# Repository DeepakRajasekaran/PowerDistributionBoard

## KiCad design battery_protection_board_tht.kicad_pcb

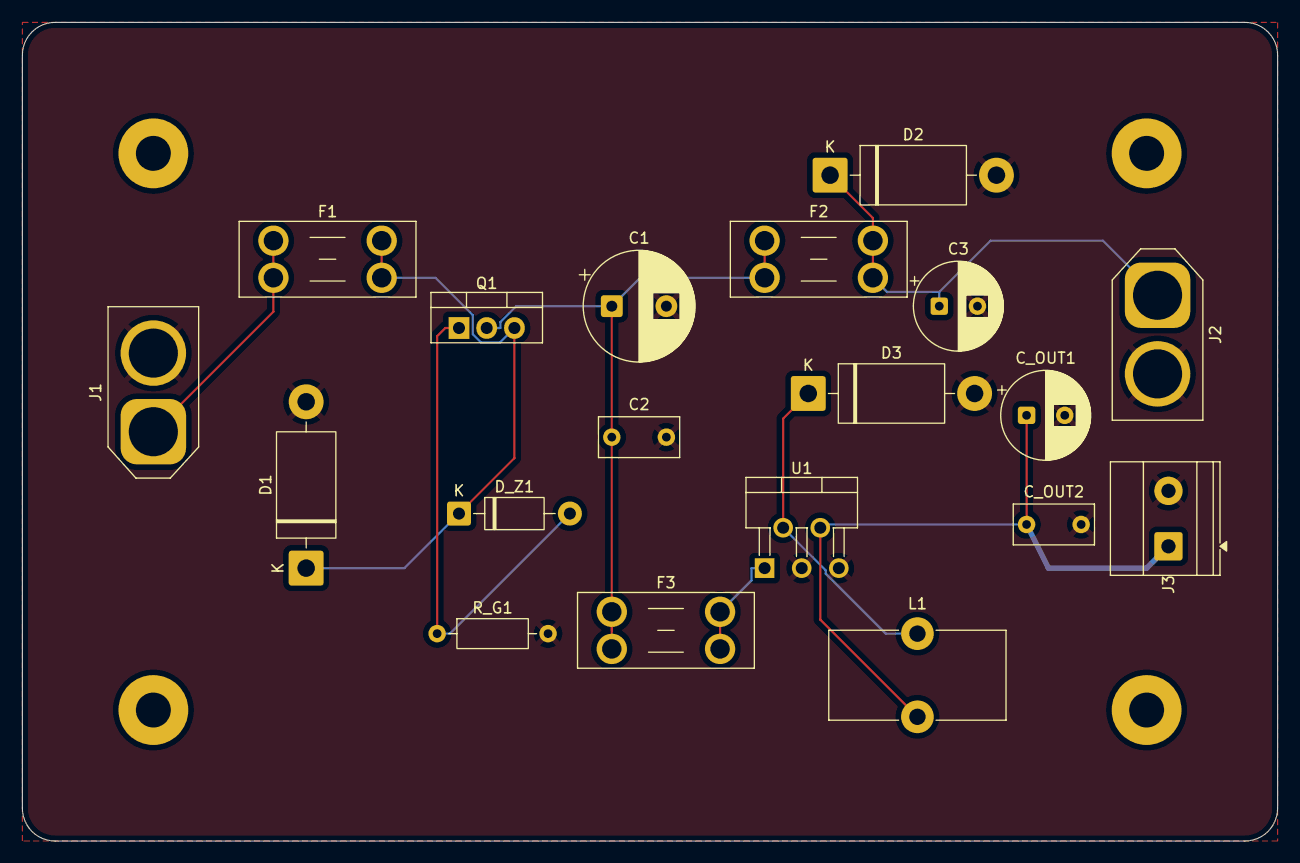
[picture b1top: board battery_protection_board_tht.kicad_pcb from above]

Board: 2 copper layers, 115.0 x 75.0 mm, 23 parts (0 on the bottom side), 9 nets.

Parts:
C1: 470uF 35V; CP_Radial_D10.0mm_P5.00mm
C2: 100nF 50V; C_Rect_L7.2mm_W3.5mm_P5.00mm_FKS2_FKP2_MKS2_MKP2
C3: 100uF 35V; CP_Radial_D8.0mm_P3.50mm
C_OUT1: 470uF 16V; CP_Radial_D8.0mm_P3.50mm
C_OUT2: 100nF 50V; C_Rect_L7.2mm_W3.5mm_P5.00mm_FKS2_FKP2_MKS2_MKP2
D1: 1.5KE18CA; D_DO-201AD_P15.24mm_Horizontal
D2: 1.5KE18A; D_DO-201AD_P15.24mm_Horizontal
D3: 1N5822; D_DO-201AD_P15.24mm_Horizontal
D_Z1: 1N4742A_12V; D_DO-41_SOD81_P10.16mm_Horizontal
F1: 15A Blade; Fuseholder_Blade_Mini_Keystone_3568
F2: 10A Blade; Fuseholder_Blade_Mini_Keystone_3568
F3: 3A Blade; Fuseholder_Blade_Mini_Keystone_3568
J1: XT60-M_BATT_IN; AMASS_XT60-M_1x02_P7.20mm_Vertical
J2: XT60-F_OUT2_10A; AMASS_XT60-F_1x02_P7.20mm_Vertical
J3: 5V_3A_TERM; TerminalBlock_Phoenix_MKDS-1,5-2-5.08_1x02_P5.08mm_Horizont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
L1: 33uH 5A; L_Toroid_Vertical_L16.0mm_W8.0mm_P7.62mm
MH1, MH2, MH3, MH4: MountingHole_3.2mm; MountingHole_3.2mm_M3_Pad
Q1: IRF4905; TO-220-3_Vertical
R_G1: 100k; R_Axial_DIN0207_L6.3mm_D2.5mm_P10.16mm_Horizontal
U1: LM2596T-5.0; TO-220-5_P3.4x3.7mm_StaggerOdd_Lead3.8mm_Vertical

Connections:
+5V: C_OUT1.1, C_OUT2.1, J3.1, L1.2, U1.4
BATT+: F1.1, J1.1
BATT_FUSED: D1.1, D_Z1.1, F1.2, Q1.3
GATE_Q1: D_Z1.2, Q1.1, R_G1.1
GND: C1.2, C2.2, C3.2, C_OUT1.2, C_OUT2.2, D1.2, D2.2, D3.2, J1.2, J2.2, J3.2, R_G1.2, U1.3, U1.5
OUT2+: C3.1, D2.1, F2.2, J2.1
SW_BUCK: D3.1, L1.1, U1.2
V_BUCK_IN: F3.2, U1.1
V_SYS: C1.1, C2.1, F2.1, F3.1, Q1.2
